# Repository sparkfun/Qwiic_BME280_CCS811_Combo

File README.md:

SparkFun CCS811/BME280 Combo Board
========================================

[*Sparkfun Environmental Combo Breakout CCS811/BME280 (SEN-14348)*](https://www.sparkfun.com/products/14348)

The SparkFun CCS811/BME280 Combo Breakout is perfect for sensing anything you may want to know about the air quality. This breakout will fine tune eCO<sub>2</sub> and tVOC readings from the CCS811 using humidity and temperature readings from the BME280. The breakout will also detect barometric pressure.

Repository Contents
-------------------

* **/Documentation** - Data sheets, additional product information
* **/Firmware** - Example code 
* **/Hardware** - Eagle design files (.brd, .sch)
* **/Libraries** - Libraries for use with the <CCS811/BME280>
* **/Production** - Production panel files (.brd)
* **/Software** - Related software for the <CCS811/BME280>

Documentation
--------------
* **[Library](https://github.com/sparkfun/SparkFun_CCS811_Arduino_Library/)** - <Arduino> library for the CCS811.
* **[Library](https://github.com/sparkfun/SparkFun_BME280_Arduino_Library/)** - <Arduino> library for the BME280.
* **[Hookup Guide](https://learn.sparkfun.com/tutorials/ccs811bme280-qwiic-environmental-combo-breakout-hookup-guide)** - Basic hookup guide for the CCS811/BME280.
* **[SparkFun Fritzing repo](https://github.com/sparkfun/Fritzing_Parts)** - Fritzing diagrams for SparkFun products.
* **[SparkFun 3D Model repo](https://github.com/sparkfun/3D_Models)** - 3D models of SparkFun products. 
* **[SparkFun Graphical Datasheets](https://github.com/sparkfun/Graphical_Datasheets)** -Graphical Datasheets for various SparkFun products.

Product Versions
----------------
* [SEN-14348](https://www.sparkfun.com/products/14348)- Breakout board for the CCS811 and BME 280 air quality sensors.

Version History
---------------
* [CCS811 - V 1.0.0](https://github.com/sparkfun/CCS811_Air_Quality_Breakout/tree/V_1.0.0) - Initial commit of Arduino compatible library for CCS811 
* [BME280 - V 1.0.0](https://github.com/sparkfun/SparkFun_BME280_Arduino_Library/tree/V_1.0.0) - Initial commit of Arduino compatible library for BME280
* [BME280 - V 1.1.0](https://github.com/sparkfun/SparkFun_BME280_Arduino_Library/tree/V_1.1.0) - Pulled request to add decimal precision to readFloatPressure() and readFloatHumidity().

License Information
-------------------

This product is _**open source**_! 

Please review the LICENSE.md file for license information. 

If you have any questions or concerns on licensing, please contact techsupport@sparkfun.com.

Distributed as-is; no warranty is given.

- Your friends at SparkFun.

_<COLLABORATION CREDIT>_

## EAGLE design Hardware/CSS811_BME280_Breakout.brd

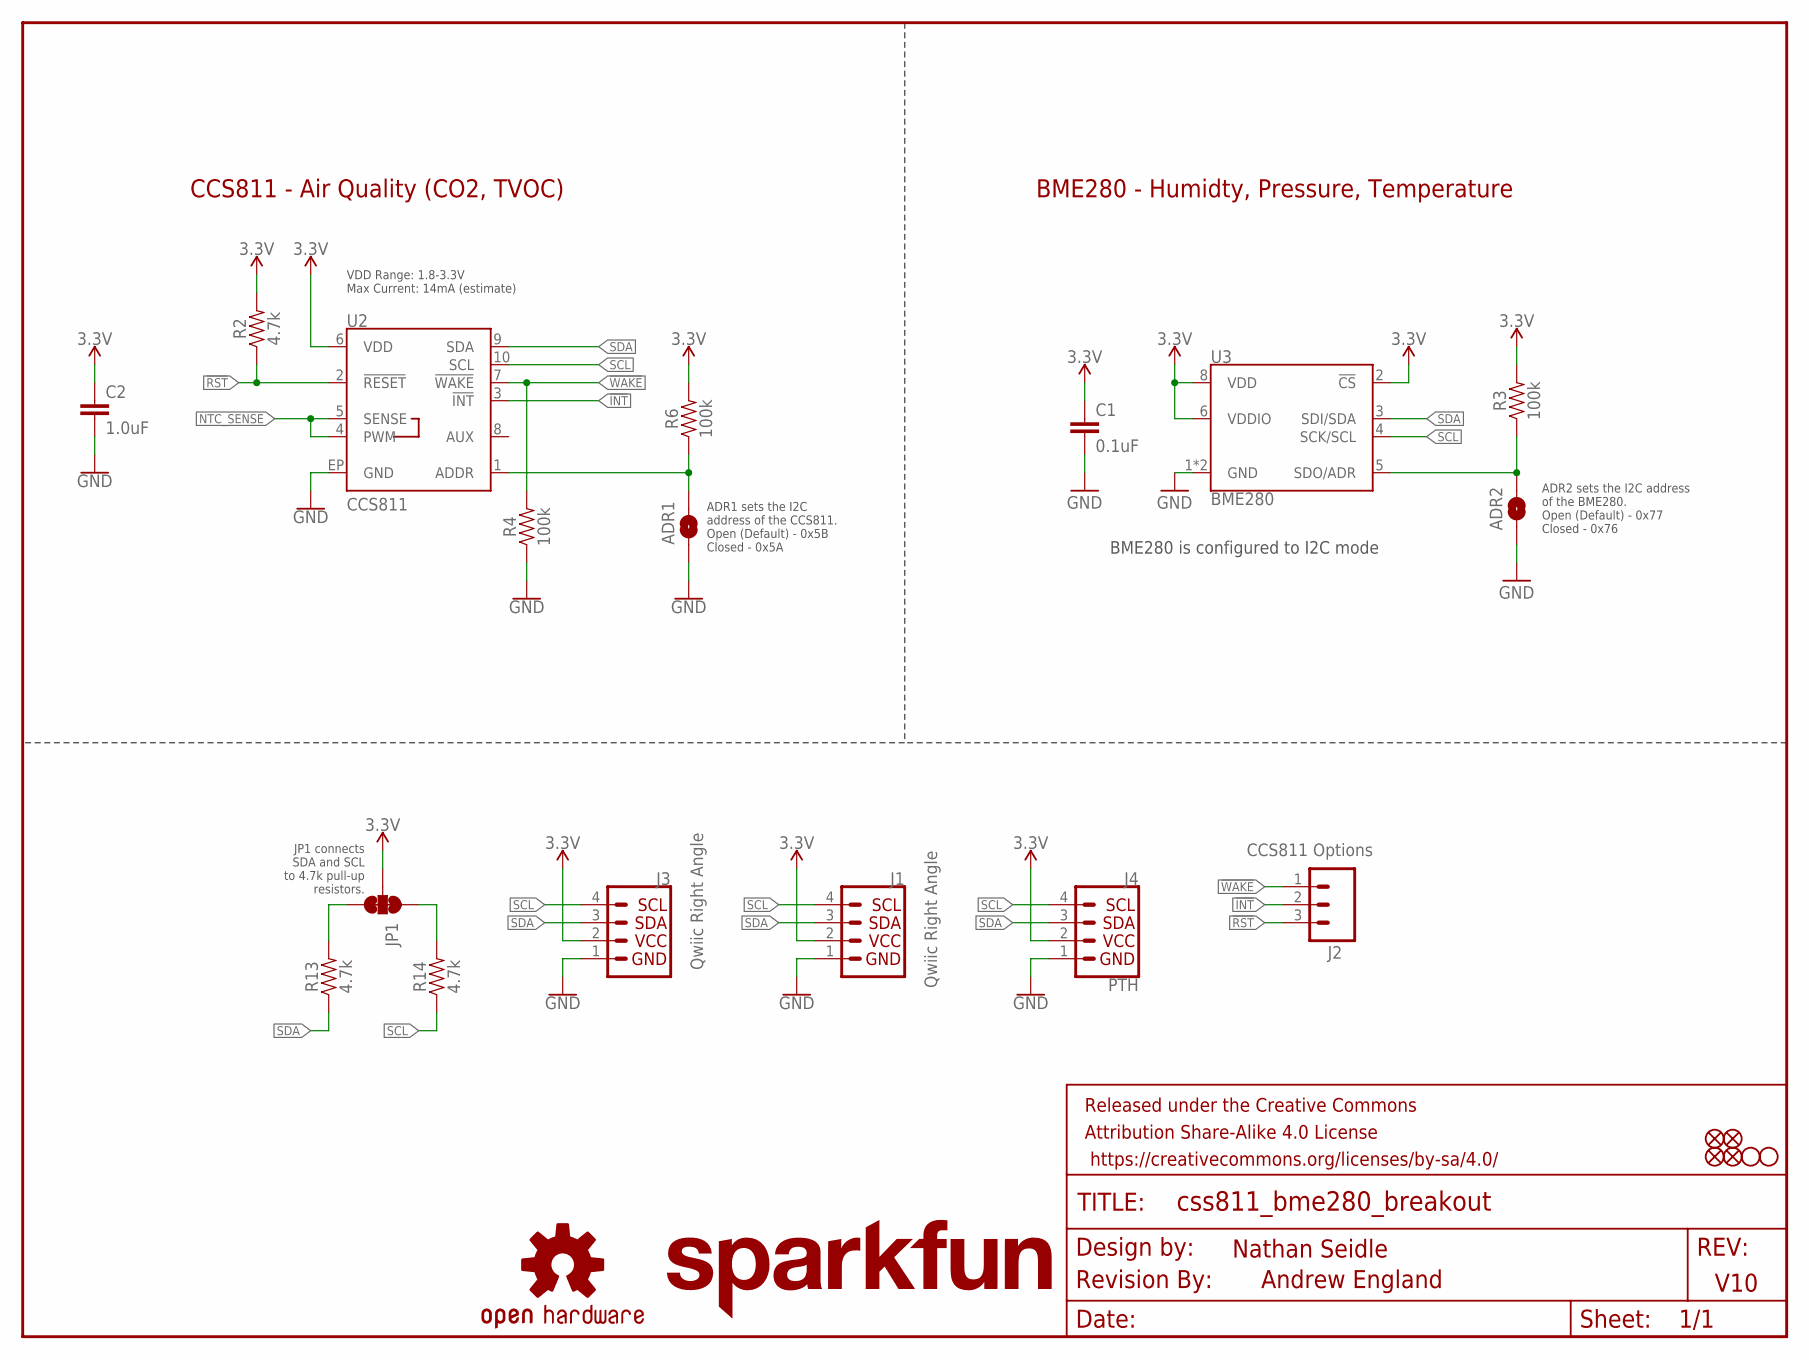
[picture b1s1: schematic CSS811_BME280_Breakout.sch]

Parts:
ADR1, ADR2: JUMPER-SMT_2_NO_SILK; SMT-JUMPER_2_NO_SILK
C1: 0.1uF; 0603
C2: 1.0uF; 0603
FD1, FD2, FD3, FD4: FIDUCIAL1X2; FIDUCIAL-1X2
FRAME1: FRAME-LETTER; CREATIVE_COMMONS
H2, H4: STAND-OFF
J1, J3: Qwiic Right Angle; 1X04_1MM_RA
J2: CCS811 Options; 1X03_NO_SILK
J4: PTH; 1X04_NO_SILK
JP1: JUMPER-SMT_3_2-NC_TRACE_SILK; SMT-JUMPER_3_2-NC_TRACE_SILK
LOGO1: SFE_LOGO_NAME.1_INCH; SFE_LOGO_NAME_.1
LOGO2: REVISION
LOGO4: OSHW-LOGOS; OSHW-LOGO-S
R2, R13, R14: 4.7k; 0603
R3, R4, R6: 100k; 0603
U2: CCS811; LGA10
U3: BME280; LGA-8-2.5X2.5

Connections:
3.3V: C1.1, C2.1, J1.2, J3.2, J4.2 (VCC), JP1.2, R2.2, R3.2, R6.2, U2.6 (VDD), U3.2 (!CS), U3.6 (VDDIO), U3.8 (VDD)
!INT: J2.2, U2.3 (!INT!)
!RST: J2.3, R2.1, U2.2 (!RESET!)
!WAKE: J2.1, R4.2, U2.7 (!WAKE!)
CCS811_ADDR: ADR1.2, R6.1, U2.1 (ADDR)
GND: ADR1.1, ADR2.1, C1.2, C2.2, J1.1, J3.1, J4.1 (GND), R4.1, U2.EP (GND), U3.1 (GND), U3.7 (GND)
unnamed: JP1.3, R13.2
unnamed: JP1.1, R14.2
NTC_SENSE: U2.4 (PWM), U2.5 (SENSE)
SCL: J1.4, J3.4, J4.4 (SCL), R14.1, U2.10 (SCL), U3.4 (SCK/SCL)
SDA: J1.3, J3.3, J4.3 (SDA), R13.1, U2.9 (SDA), U3.3 (SDI/SDA)
SDO/ADR: ADR2.2, R3.1, U3.5 (SDO/ADR)

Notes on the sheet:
VDD Range: 1.8-3.3V Max Current: 14mA (estimate)
CCS811 - Air Quality (CO2, TVOC)
ADR1 sets the I2C address of the CCS811. Open (Default) - 0x5B Closed - 0x5A
JP1 connects SDA and SCL to 4.7k pull-up resistors.
V10
Nathan Seidle
ADR2 sets the I2C address of the BME280. Open (Default) - 0x77 Closed - 0x76
BME280 is configured to I2C mode
BME280 - Humidty, Pressure, Temperature
Andrew England

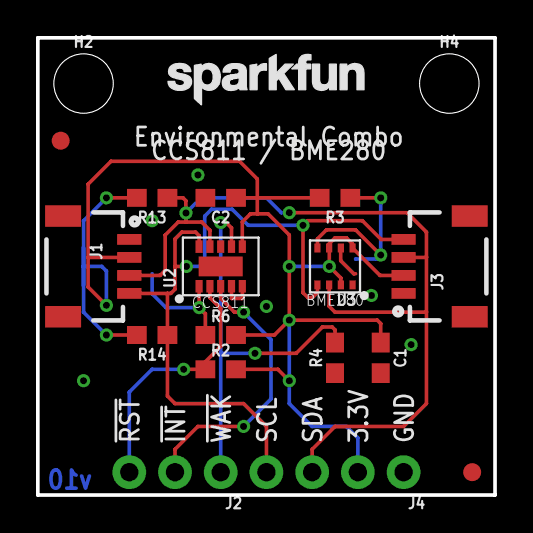
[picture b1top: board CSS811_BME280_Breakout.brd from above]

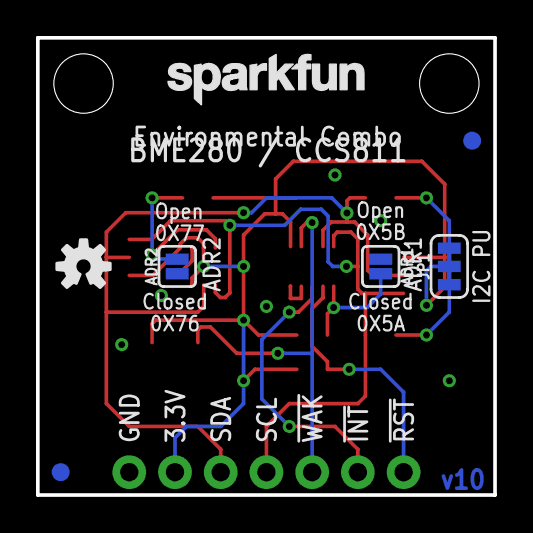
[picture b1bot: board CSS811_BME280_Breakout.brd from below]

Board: 2 copper layers, 25.4 x 25.4 mm, 28 parts (7 on the bottom side), 12 nets.

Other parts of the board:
LOGO3: SFE_LOGO_NAME.1_INCH; SFE_LOGO_NAME_.1

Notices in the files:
parts and their libraries:
SparkFun-Aesthetics: Licensing: Creative Commons ShareAlike 4.0 International - https://creativecommons.org/licenses/by-sa/4.0
SparkFun-Aesthetics: Released under the Creative Commons Attribution Share-Alike 4.0 License
SparkFun-Aesthetics: https://creativecommons.org/licenses/by-sa/4.0
